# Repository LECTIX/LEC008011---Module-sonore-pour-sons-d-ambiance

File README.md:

# LEC008011 - Module sonore pour sons d’ambiance
Fichiers sources pour le produit LEC008011

## Description du produit

Branchez jusqu’à 14 boutons poussoirs, ILS, relais ou encore pédales de contact pour déclencher des sons personnalisés et donner vie à votre réseau.

## Utiliser les fichiers sources pour fabriquer le produit

Grâce aux fichiers sources publiés ici, vous pouvez être en mesure de faire fabriquer ce produit par un sous traitant.

**ATTENTION** ce produit est un **produit complexe à fabriquer** et nécessite notamment une programmation afin de pouvoir fonctionner. Vous devez pour cela posséder le programmateur et programmer vous même la carte. Cette étape peut nécessiter des connaissances techniques, si nécessaire, nous vous encourrageons à vous rapprocher d'un club.

**Remarque** ce produit est composé d'une carte mère, d'un haut parleur externe (8 ohm 1W, référence FS50MS0810-H7.5), d'une carte micro SD, et d'un module pour la gestion du son (DF-player mini). Ce dossier permet uniquement de faire fabriquer la carte mère, vous devrez vous fournir les autres composants sur un site de revente (amazon, aliexpress, mouser, ...).

### Faire fabriquer chez un sous traitant

Il est aujourd'hui possible de faire fabriquer à moindre cout des cartes électroniques. Nous recommendons [JLCPCB](https://jlcpcb.com/) si vous voulez aller au moins cher. Si vous préférez un acteur européen, [eurocircuits](https://www.eurocircuits.com/) est un des acteurs reconnus.

1. Télécherger les sources de ce produit en cliquant sur le bouton `Code`, puis `Download ZIP`.
1. Décompresser le dossier.
1. Les fichiers pour la fabrication se trouvent dans le répertoire `hardware/prod`.
1. Se connecter sur [https://cart.jlcpcb.com/quote](https://cart.jlcpcb.com/quote)
1. Cliquer sur le bouton `Add gerber file` et sélectionner le fichier `gerbers.zip`.
1. Sélectionnez la quantité de cartes que vous souhaitez dans le champs `PCB Qty`.
1. Laisser toutes les autres options par défaut, puis cliquez sur le toggle switch en face de `PCB Assembly`, et enfin sur le bouton `confirm`.
1. Une preview de la carte électronique sans les composants doit apparaitre. Cliquez sur `NEXT`.
1. Cliquez sur le bouton `Add BOM File`, puis sélectionnez le fichier `bom.csv`
1. Cliquez sur le bouton `Add CPL File`, puis sélectionnez le fichier `pos.csv`
1. **Vérifier que tous les composants sont en stock** et bien sélectionnés, puis cliquez sur `NEXT`.
1. Une preview de la carte avec ses composants apparait. Continuer le chemin en cliquant sur `NEXT`.
1. Le prix final apparait. Sélectionnez la catégorie du produit, puis cliquez sur `SAVE TO CART`.
1. Une fois sauvegardé dans votre panier, vous pouvez valider votre commande et choisir le moyen d'acheminement. Afin de ne pas avoir à se préoccuper des frais de douane, nous vous conseillons de choisir une méthode d'expédition DDP.

Vous receverez vos cartes sous 1 à 3 semaines. 

**Nous ne sommes en aucun cas responsables des cartes qui arriveraient défectueuses ou non fonctionnelles.**

### Modifications des fichiers sources

Installez kicad 6 (ou version supérieure), et ouvrez le fichier LEC008011.kicad_pro

### Programation

Pour programmer le module, vous devez posséder
- un programmateur AVR type USBASP
- Un adaptateur 10 pin vers 6 pin
- Un connecteur de type header 2 x 6 pour connecter l'adaptateur à la carte

Le firmware se trouve dans le dossier du même nom. Il est recommandé d'utiliser VS-code et platform-io pour programmer la carte. Pour ce faire, branchez le programmateur à votre PC et à la carte à programmer, puis rentrer les commandes suivantes :

```
cd firmware
platformio run --target fuses && platformio run --target upload
```

### Regénérer les fichiers gerber, BOM, et position (Optionnel)

Peut se faire simplement en utilisant kikit :

```
cd hardware
docker run --rm -w /kikit -v $PWD:/kikit yaqwsx/kikit kikit fab jlcpcb --assembly --no-drc --schematic LEC008011.kicad_sch --field LCSC --corrections JLCPCB_CORRECTION --nametemplate LEC008011_{} LEC008011.kicad_pcb prod/

```
## Notices
[Manuel FR](docs/manual_fr.pdf)

## License
Tous nos fichiers sont plubliés sous les licenses
- CERN Open Hardware Licence Version 2 - Strongly Reciprocal pour ce qui touche au hardware
- GNU General Public License v3.0 pour tout ce qui est software

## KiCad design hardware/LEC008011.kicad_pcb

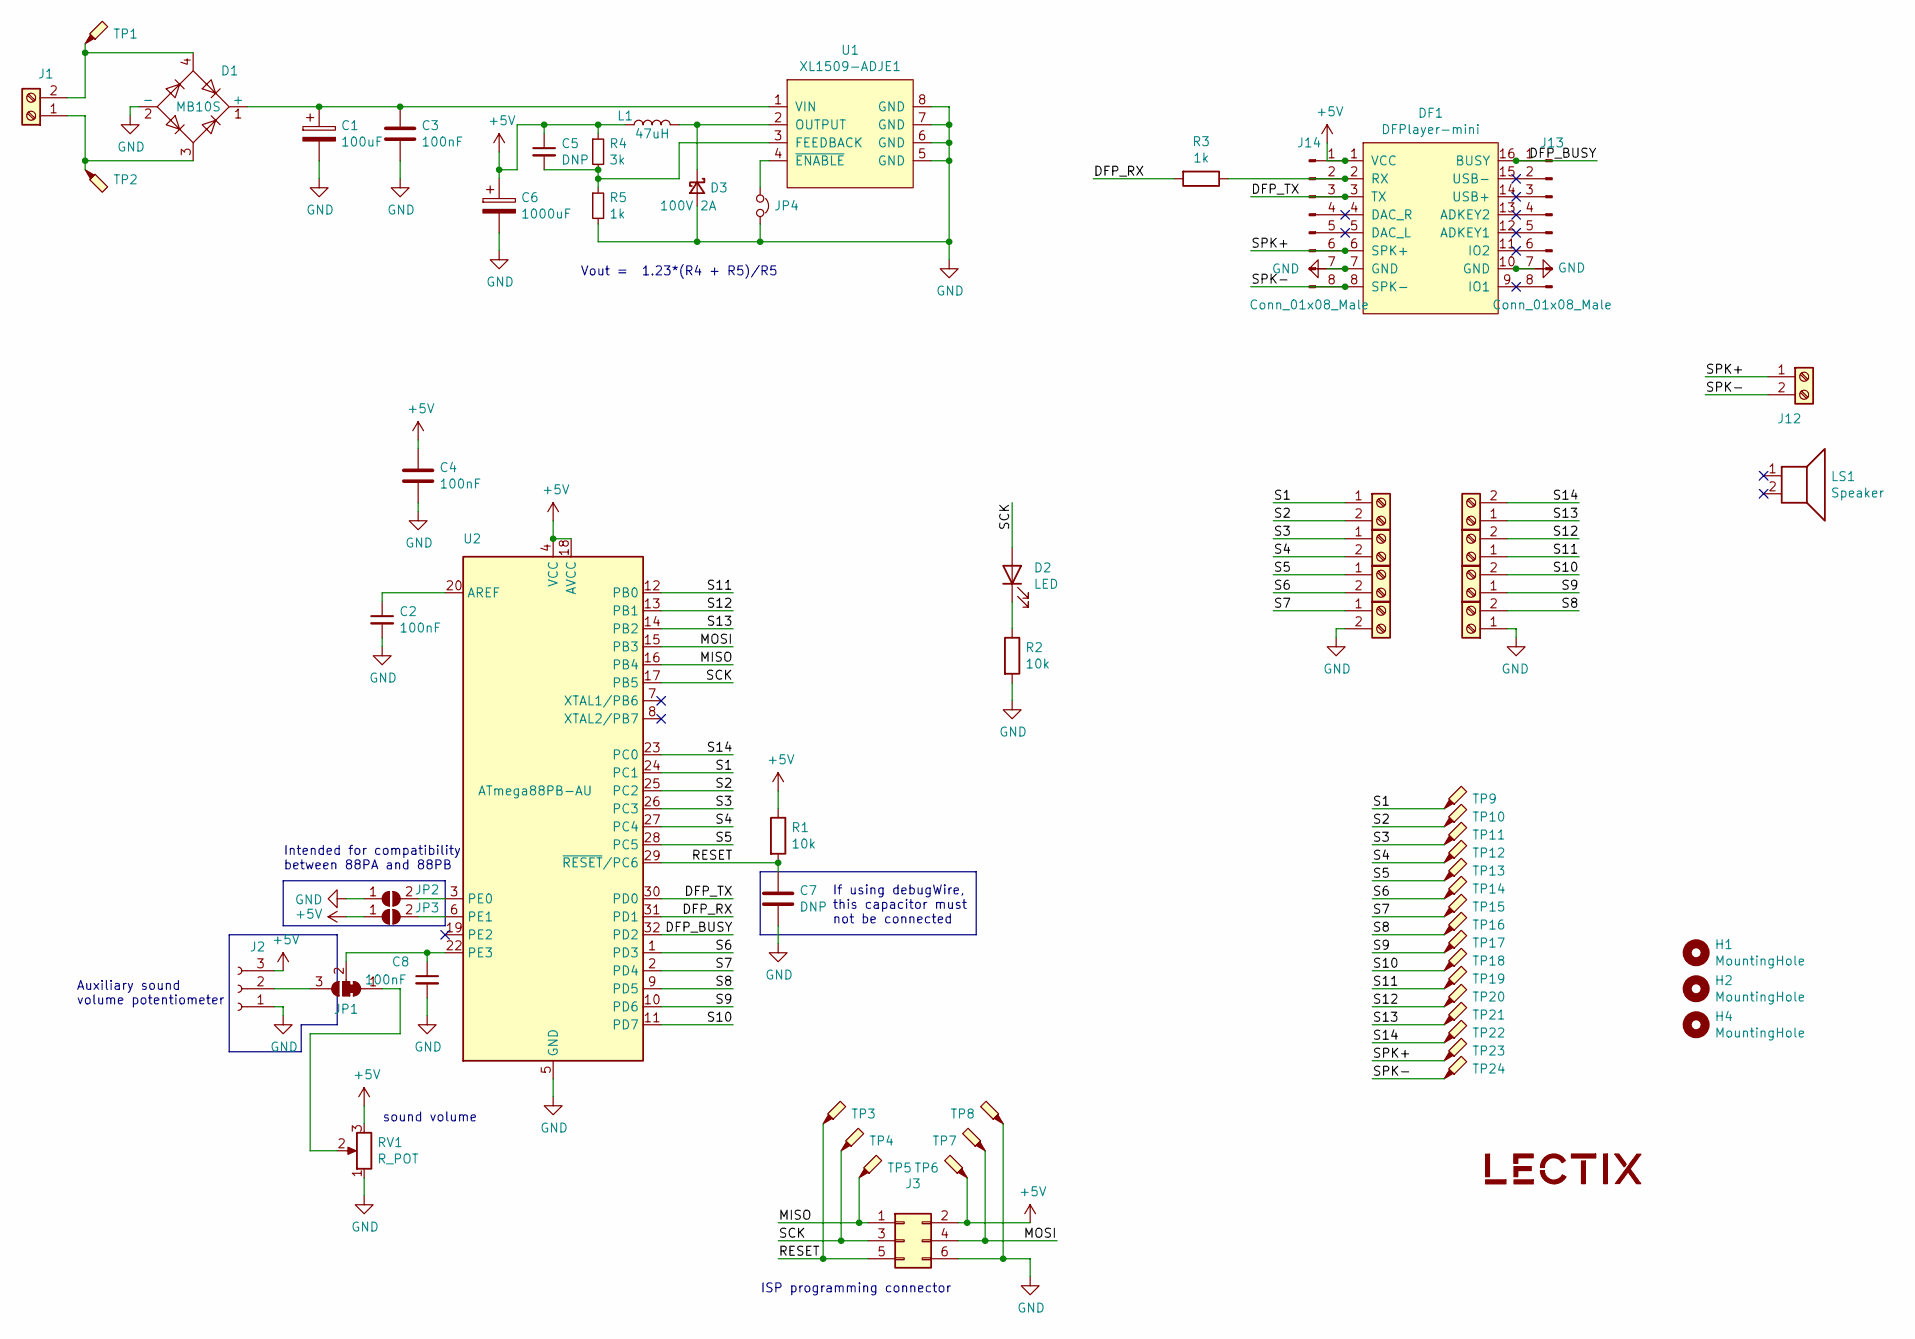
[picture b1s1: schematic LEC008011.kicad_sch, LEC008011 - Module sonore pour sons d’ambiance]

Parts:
C1: 100uF; CP_Elec_6.3x7.7; MPN VZT101M1VTR-0606; LCSC C249982
C2, C3, C4, C8: 100nF; C_0805_2012Metric; MPN CC0805KRX7R9BB104; LCSC C49678
C5, C7: DNP; C_0805_2012Metric; MPN DNP; LCSC DNP
C6: 1000uF; CP_Elec_8x10.5; MPN VEJ471M1CTR-0810; LCSC C176671
D1: MB10S; TO-269AA; MPN MB10S; LCSC C2488
D2: LED; LED_0603_1608Metric; MPN 19-217/GHC-YR1S2/3T; LCSC C72043
D3: 100V 2A; D_SMA; MPN SS210; LCSC C14996
DF1: DFPlayer-mini; DFPlayer; MPN Female Header 8P, 2.54mm pitch; LCSC C27438
H1, H2, H4: MountingHole; MountingHole_3.2mm_M3; MPN DNP; LCSC DNP
J1: Screw_Terminal_01x02; TerminalBlock_bornier-2_P5.08mm-green; MPN DB126V-5.0-2P-GN; LCSC C395849
J2: Conn_01x03_Female; SolderWirePad_1x03_P3.81mm_Drill1.2mm; MPN DNP; LCSC DNP
J3: Conn_02x03_Odd_Even; PinHeader_2x03_P2.54mm_Vertical; MPN DNP; LCSC C5116479
J4, J5, J6, J7, J8, J9, J10, J11, J12: Screw_Terminal_01x02; TerminalBlock_bornier-2_P5.08mm-blue; MPN DB301V-5.0-2P-BU-S; LCSC C395882
J13, J14: Conn_01x08_Male; PinHeader_1x08_P2.54mm_Vertical; LCSC C27438
JP1: SolderJumper_3_Bridged12; SolderJumper-3_P1.3mm_Bridged12_RoundedPad1.0x1.5mm; MPN DNP; LCSC DNP
JP2, JP3: SolderJumper_2_Open; SolderJumper-2_P1.3mm_Open_RoundedPad1.0x1.5mm; MPN DNP; LCSC DNP
JP4: Jumper_NC_Small; SolderJumper-2_P1.3mm_Bridged_RoundedPad1.0x1.5mm; MPN DNP; LCSC DNP
L1: 47uH; JSHC0650-470M; MPN JSHC0650-470M; LCSC C386872
LOGO1: logo_lectix_25mm; Logo_10mm; MPN DNP; LCSC DNP
LS1: Speaker; MPN FS50MS0810-H7.5; LCSC C482318
R1, R2: 10k; R_0805_2012Metric; MPN 0805W8F1002T5E; LCSC C17414
R3, R5: 1k; R_0805_2012Metric; MPN 0805W8F1001T5E; LCSC C17513
R4: 3k; R_0805_2012Metric; MPN 0805W8F3001T5E; LCSC C17661
RV1: R_POT; Potentiometer_Bourns_TC33X_Vertical; MPN VG039NCHXTB153; LCSC C128547
TP1, TP2, TP3, TP4, TP5, TP6, TP7, TP8, TP9, TP10, TP11, TP12, TP13, TP14, TP15, TP16, TP17, TP18, TP19, TP20, TP21, TP22, TP23, TP24: TestPoint_Probe; TestPoint_Pad_D1.0mm; MPN DNP; LCSC DNP
U1: XL1509-ADJE1; SOP-8_3.76x4.96mm_P1.27mm; MPN XL1509-ADJE1; LCSC C74192
U2: ATmega88PB-AU; TQFP-32_7x7mm_P0.8mm; MPN ATMEGA88PA-AU; LCSC C8727

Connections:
+5V: C4.1, C5.1, C6.1, DF1.1 (VCC), J2.3, J3.2, J14.1, JP3.1 (A), L1.1, R1.1, R4.1, RV1.3, TP6.1, U2.4 (VCC), U2.18 (AVCC)
/DFP_BUSY: DF1.16 (BUSY), J13.1, U2.32 (PD2)
/DFP_RX: R3.2, U2.31 (PD1)
/DFP_TX: DF1.3 (TX), J14.3, U2.30 (PD0)
/MISO: J3.1, TP5.1, U2.16 (PB4)
/MOSI: J3.4, TP7.1, U2.15 (PB3)
/RESET: C7.1, J3.5, R1.2, TP3.1, U2.29 (~RESET/PC6)
/S1: J4.1, TP9.1, U2.24 (PC1)
/S2: J4.2, TP10.1, U2.25 (PC2)
/S3: J5.1, TP11.1, U2.26 (PC3)
/S4: J5.2, TP12.1, U2.27 (PC4)
/S5: J6.1, TP13.1, U2.28 (PC5)
/S6: J6.2, TP14.1, U2.1 (PD3)
/S7: J7.1, TP15.1, U2.2 (PD4)
/S8: J11.2, TP16.1, U2.9 (PD5)
/S9: J10.1, TP17.1, U2.10 (PD6)
/S10: J10.2, TP18.1, U2.11 (PD7)
/S11: J9.1, TP19.1, U2.12 (PB0)
/S12: J9.2, TP20.1, U2.13 (PB1)
/S13: J8.1, TP21.1, U2.14 (PB2)
/S14: J8.2, TP22.1, U2.23 (PC0)
/SCK: D2.2 (A), J3.3, TP4.1, U2.17 (PB5)
/SPK+: DF1.6 (SPK+), J12.1, J14.6, TP23.1
/SPK-: DF1.8 (SPK-), J12.2, J14.8, TP24.1
GND: C1.2, C2.2, C3.2, C4.2, C6.2, C7.2, C8.2, D1.2 (-), D3.2 (A), DF1.7 (GND), DF1.10 (GND), J2.1, J3.6, J7.2, J11.1, J13.7, J14.7, JP2.1 (A), JP4.2, R2.2, R5.2, RV1.1, TP8.1, U1.5 (GND), U1.6 (GND), U1.7 (GND), U1.8 (GND), U2.5 (GND), U2.21 (GND)
unnamed: C1.1, C3.1, D1.1 (+), U1.1 (VIN)
unnamed: C2.1, U2.20 (AREF)
unnamed: C5.2, R4.2, R5.1, U1.3 (FEEDBACK)
unnamed: C8.1, JP1.2 (C), U2.22 (PE3)
unnamed: D1.3, J1.1, TP2.1
unnamed: D1.4, J1.2, TP1.1
unnamed: D2.1 (K), R2.1
unnamed: D3.1 (K), L1.2, U1.2 (OUTPUT)
unnamed: DF1.2 (RX), J14.2, R3.1
unnamed: DF1.4 (DAC_R), J14.4
unnamed: DF1.5 (DAC_L), J14.5
unnamed: DF1.9 (IO1), J13.8
unnamed: DF1.11 (IO2), J13.6
unnamed: DF1.12 (ADKEY1), J13.5
unnamed: DF1.13 (ADKEY2), J13.4
unnamed: DF1.14 (USB+), J13.3
unnamed: DF1.15 (USB-), J13.2
unnamed: J2.2, JP1.3 (B)
unnamed: JP1.1 (A), RV1.2
unnamed: JP2.2 (B), U2.3 (PE0)
unnamed: JP3.2 (B), U2.6 (PE1)
unnamed: JP4.1, U1.4 (~ENABLE)

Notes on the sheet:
sound volume
Vout = 1.23*(R4 + R5)/R5
Auxiliary sound volume potentiometer
If using debugWire, this capacitor must not be connected
ISP programming connector
Intended for compatibility between 88PA and 88PB

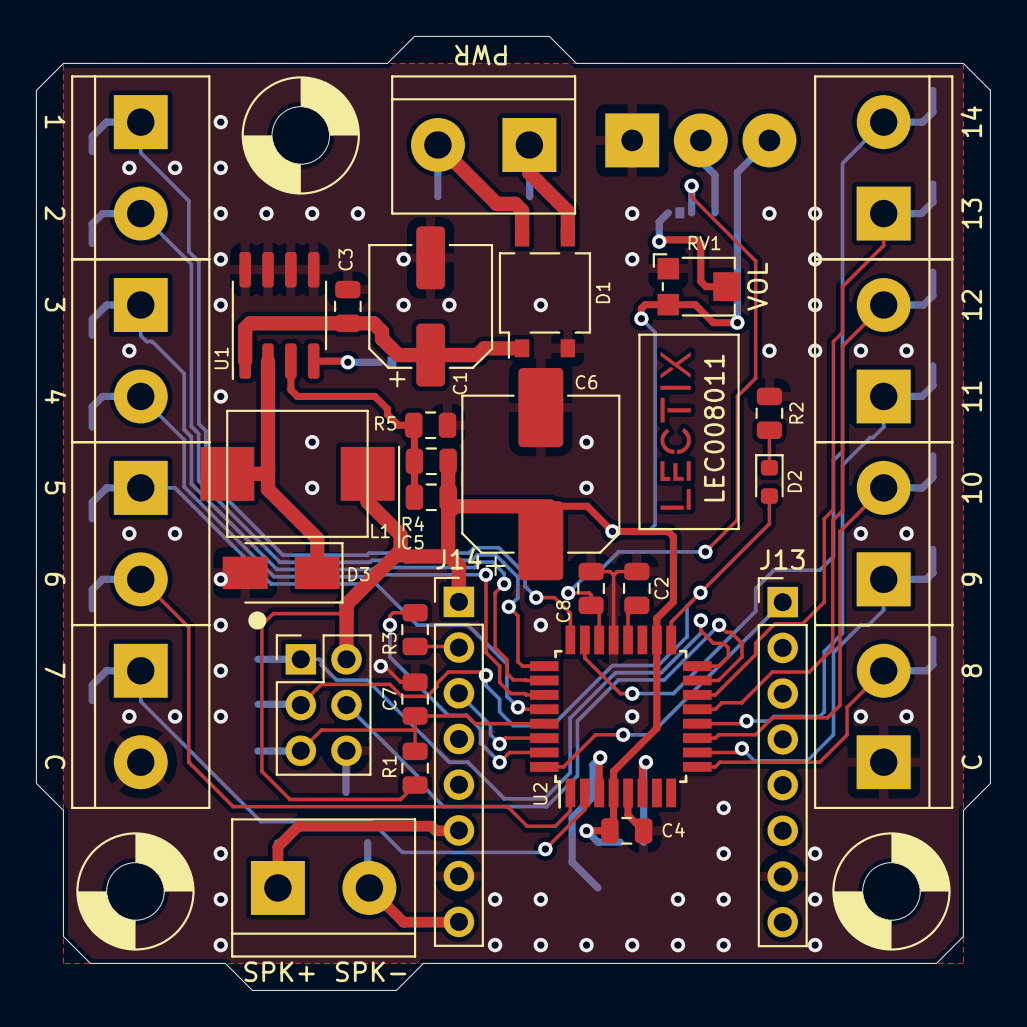
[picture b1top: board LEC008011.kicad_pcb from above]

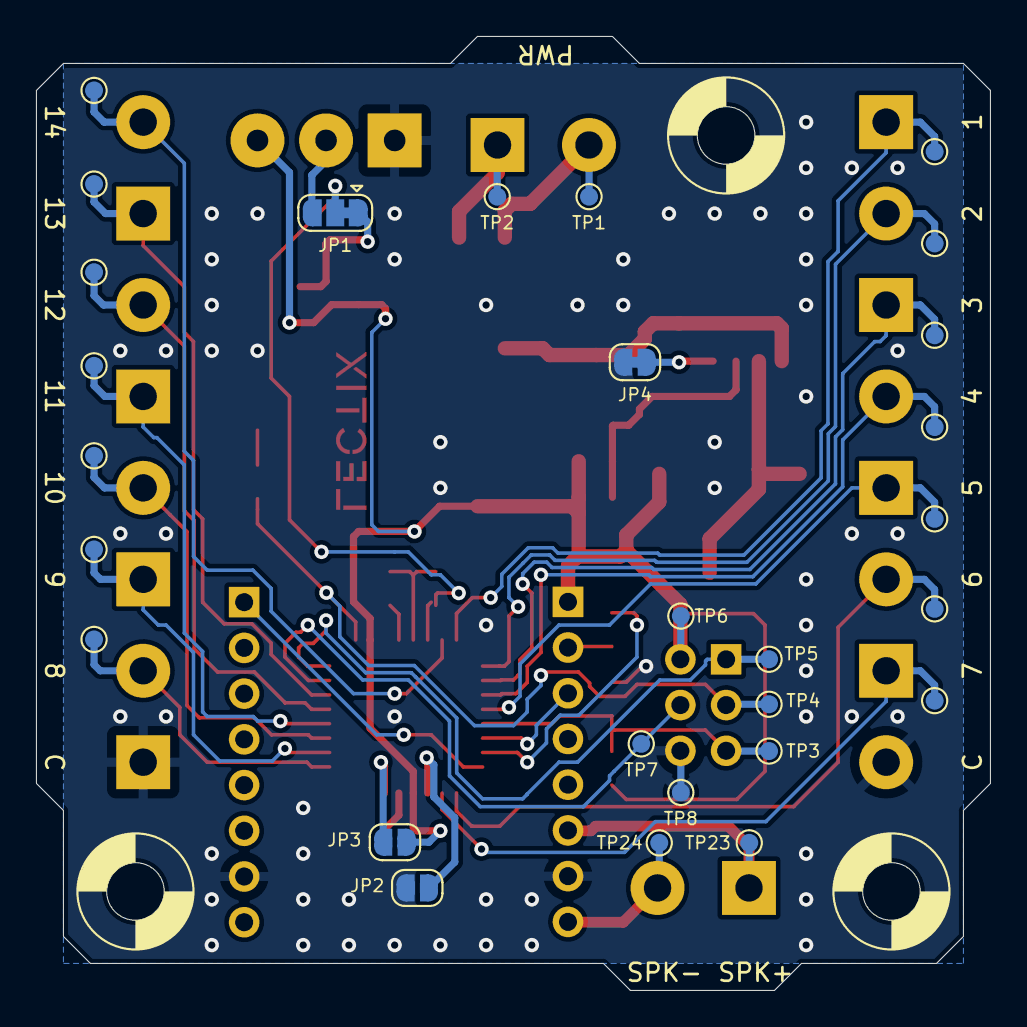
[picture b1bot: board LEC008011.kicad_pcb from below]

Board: 2 copper layers, 53.0 x 53.0 mm, 66 parts (28 on the bottom side), 39 nets.

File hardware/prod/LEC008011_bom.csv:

Comment,Designator,Footprint,LCSC
100uF,C1,Capacitor_SMD:CP_Elec_6.3x7.7,C249982
100nF,"C2,C3,C4,C8",Capacitor_SMD:C_0805_2012Metric,C49678
1000uF,C6,Capacitor_SMD:CP_Elec_8x10.5,C176671
MB10S,D1,Package_TO_SOT_SMD:TO-269AA,C2488
LED,D2,LED_SMD:LED_0603_1608Metric,C72043
100V 2A,D3,Diode_SMD:D_SMA,C14996
Screw_Terminal_01x02,J1,0_connectors:TerminalBlock_bornier-2_P5.08mm-green,C395849
Conn_02x03_Odd_Even,J3,Connector_PinHeader_2.54mm:PinHeader_2x03_P2.54mm_Vertical,C5116479
Screw_Terminal_01x02,"J4,J5,J6,J7,J8,J9,J10,J11,J12",0_connectors:TerminalBlock_bornier-2_P5.08mm-blue,C395882
Conn_01x08_Male,"J13,J14",Connector_PinHeader_2.54mm:PinHeader_1x08_P2.54mm_Vertical,C27438
47uH,L1,0_inductors:JSHC0650-470M,C386872
10k,"R1,R2",Resistor_SMD:R_0805_2012Metric,C17414
1k,"R3,R5",Resistor_SMD:R_0805_2012Metric,C17513
3k,R4,Resistor_SMD:R_0805_2012Metric,C17661
R_POT,RV1,0_potentiometers:Potentiometer_Bourns_TC33X_Vertical,C128547
XL1509-ADJE1,U1,Package_SO:SOP-8_3.76x4.96mm_P1.27mm,C74192
ATmega88PB-AU,U2,Package_QFP:TQFP-32_7x7mm_P0.8mm,C8727

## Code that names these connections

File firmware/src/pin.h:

#ifndef PIN_H
#define PIN_H

#define NB_SWITCHES     14

#define PIN_LED         13    // PB5
#define PIN_DFP_TX      0     // PD0
#define PIN_DFP_RX      1     // PD1
#define PIN_DFP_BUSY    2     // PD2
const uint8_t PIN_SWITCHES[NB_SWITCHES] = {15, 16, 17, 18, 19, 3, 4, 5, 6, 7, 8, 9, 10, 14};
#define PIN_SOUND_VOL   A7    // PE3

#endif

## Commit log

2023-04-24 Add manual
2023-04-24 Add hardware source files
2023-04-24 Add pdf schematic file
2023-04-24 Add firmware files
